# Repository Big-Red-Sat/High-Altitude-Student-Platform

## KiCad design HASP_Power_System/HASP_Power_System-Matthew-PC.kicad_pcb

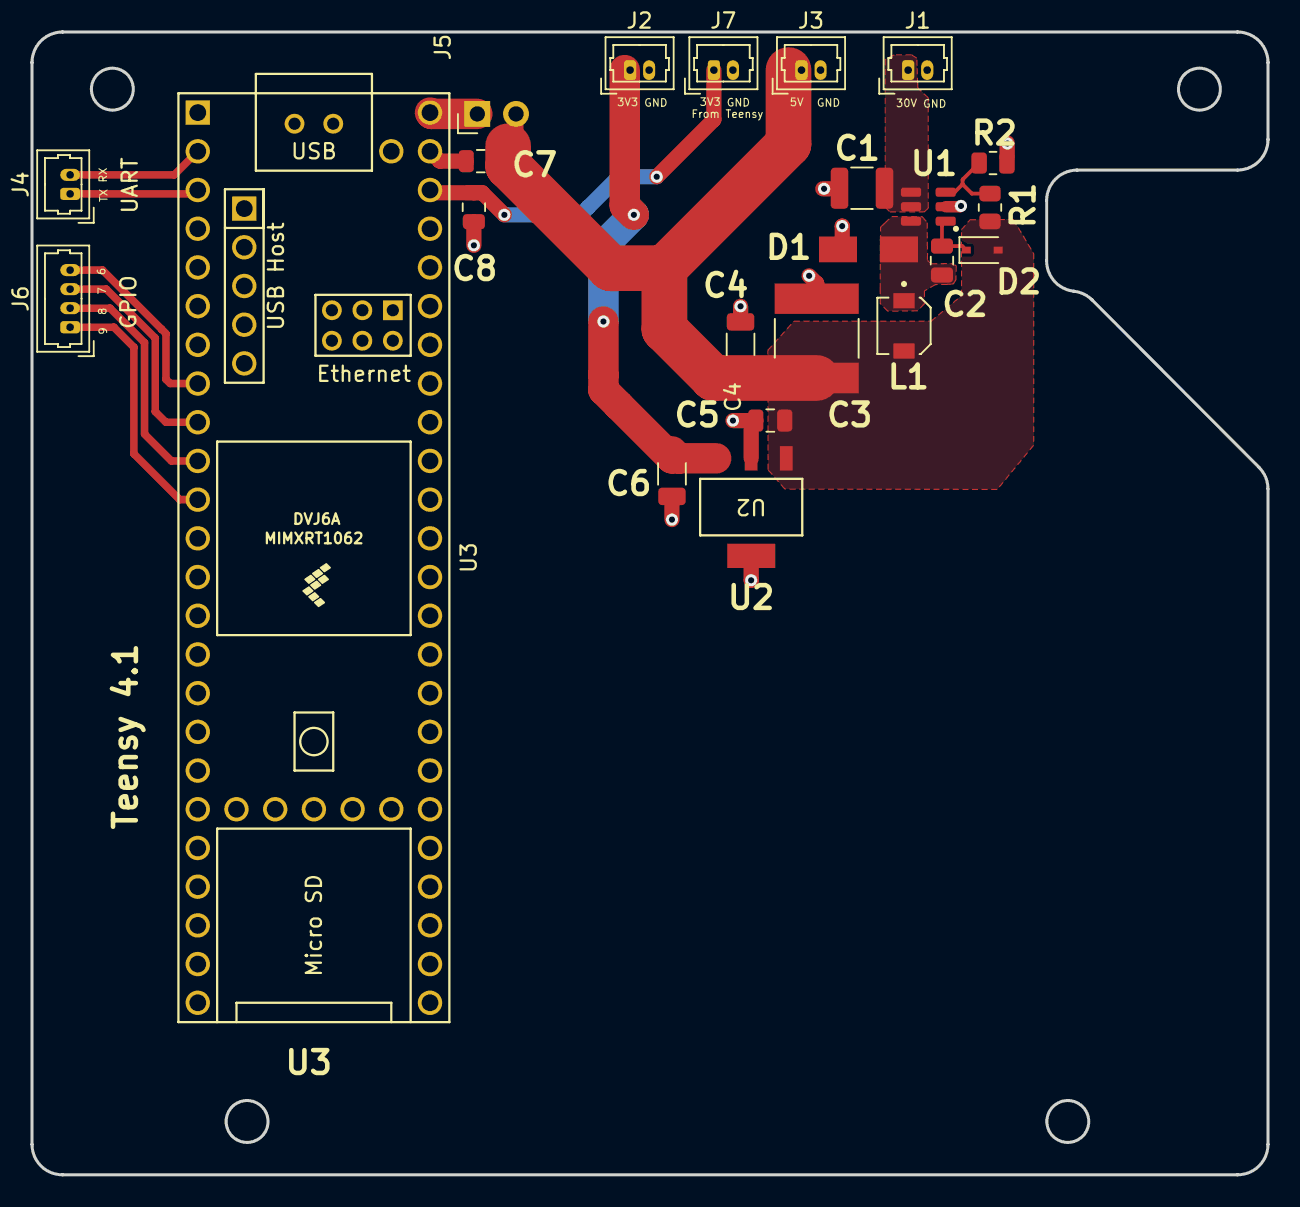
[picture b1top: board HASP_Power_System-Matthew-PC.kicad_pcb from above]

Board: 2 copper layers, 81.1 x 75.0 mm, 23 parts (0 on the bottom side), 15 nets.

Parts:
C1: 10uF; C_1210_3225Metric
C2: 100nF; C_0805_2012Metric
C3: KRM55TR71H226MH01K; CAPC6153X500N
C4: 10uF; C_1206_3216Metric
C5: 0.47uF; C_0805_2012Metric
C6: 33uF; C_1206_3216Metric
C7, C8: 0.1u; C_0805_2012Metric
D1: D_Schottky; schottky_diode_B140-13-F
D2: 1N4148; D_SOD-323
J1, J2, J3, J4, J7: Conn_01x02; Molex_PicoBlade_53047-0210_1x02_P1.25mm_Vertical
J5: Conn_01x02; PinHeader_1x02_P2.54mm_Horizontal
J6: Conn_01x04; Molex_PicoBlade_53047-0410_1x04_P1.25mm_Vertical
L1: 1231AS-H-150M=P3; IND_1231AS-H-150M=P3
R1: 51.2k; R_0805_2012Metric
R2: 10k; R_0805_2012Metric
U1: mcp16301
U2: LM3940IMPX-3.3/NOPB; MP04A
U3: Teensy4.1; Teensy41

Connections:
+3V3_LDO: C6.1, J2.1, U2.3 (OUT)
+3V3_Teensy: C8.1, J7.1, U3.46 (3V3)
+5V: C3.1, C4.1, C5.1, C7.1, D2.2 (A), J3.1, J5.2, L1.2, R1.1, U2.1 (IN)
/SW_NODE: C2.2, D1.1 (K), L1.1, U1.6 (SW)
GND: C1.2, C3.2, C4.2, C5.2, C6.2, C7.2, C8.2, D1.2 (A), J1.2, J2.2, J3.2, J7.2, R2.2, U1.2 (GND), U2.2 (GND), U3.1 (GND), U3.34 (GND), U3.47 (GND)
GPIO1: J6.4, U3.8 (6_OUT1D)
GPIO2: J6.3, U3.9 (7_RX2_OUT1A)
GPIO3: J6.2, U3.10 (8_TX2_IN1)
GPIO4: J6.1, U3.11 (9_OUT1C)
unnamed: C2.1, D2.1 (K), U1.1 (Boost)
unnamed: J5.1, U3.48 (VIN)
unnamed: R1.2, R2.1, U1.3 (V_{FB})
RX: J4.2, U3.2 (0_RX1_CRX2_CS1)
TX: J4.1, U3.3 (1_TX1_CTX2_MISO1)
VCC_30: C1.1, J1.1, U1.4 (EN), U1.5 (V_{IN})

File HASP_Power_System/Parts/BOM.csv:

Reference,Qty,Value,Footprint,Datasheet
C1,1,10uF,Capacitor_SMD:C_1210_3225Metric,
C2,1,100nF,Capacitor_SMD:C_0805_2012Metric,
C3,1,KRM55TR71H226MH01K,KRM55TR71H226MH01K:CAPC6153X500N,
C4,1,10uF,Capacitor_SMD:C_1206_3216Metric,
C5,1,0.47uF,Capacitor_SMD:C_0805_2012Metric,
C6,1,33uF,Capacitor_SMD:C_1206_3216Metric,https://www.digikey.com/en/products/detail/kyocera-avx/TPSA3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
"C7,C8",2,0.1u,Capacitor_SMD:C_0805_2012Metric,
D1,1,D_Schottky,mcp16301:schottky_diode_B140-13-F,
D2,1,1N4148,Diode_SMD:D_SOD-323,
"J1,J2,J3,J4,J7",5,Conn_01x02,Connector_Molex:Molex_PicoBlade_53047-0210_1x02_P1.25mm_Vertical,
J5,1,Conn_01x02,Connector_PinHeader_2.54mm:PinHeader_1x02_P2.54mm_Horizontal,
J6,1,Conn_01x04,Connector_Molex:Molex_PicoBlade_53047-0410_1x04_P1.25mm_Vertical,
L1,1,1231AS-H-150M=P3,1231AS_H_150M_P3:IND_1231AS-H-150M=P3,
R1,1,51.2k,Resistor_SMD:R_0805_2012Metric,
R2,1,10k,Resistor_SMD:R_0805_2012Metric,
U1,1,mcp16301,mcp16301:mcp16301,
U2,1,LM3940IMPX-3.3/NOPB,MP04A,LM3940IMPX-3.3/NOPB
U3,1,Teensy4.1,Teensy:Teensy41,

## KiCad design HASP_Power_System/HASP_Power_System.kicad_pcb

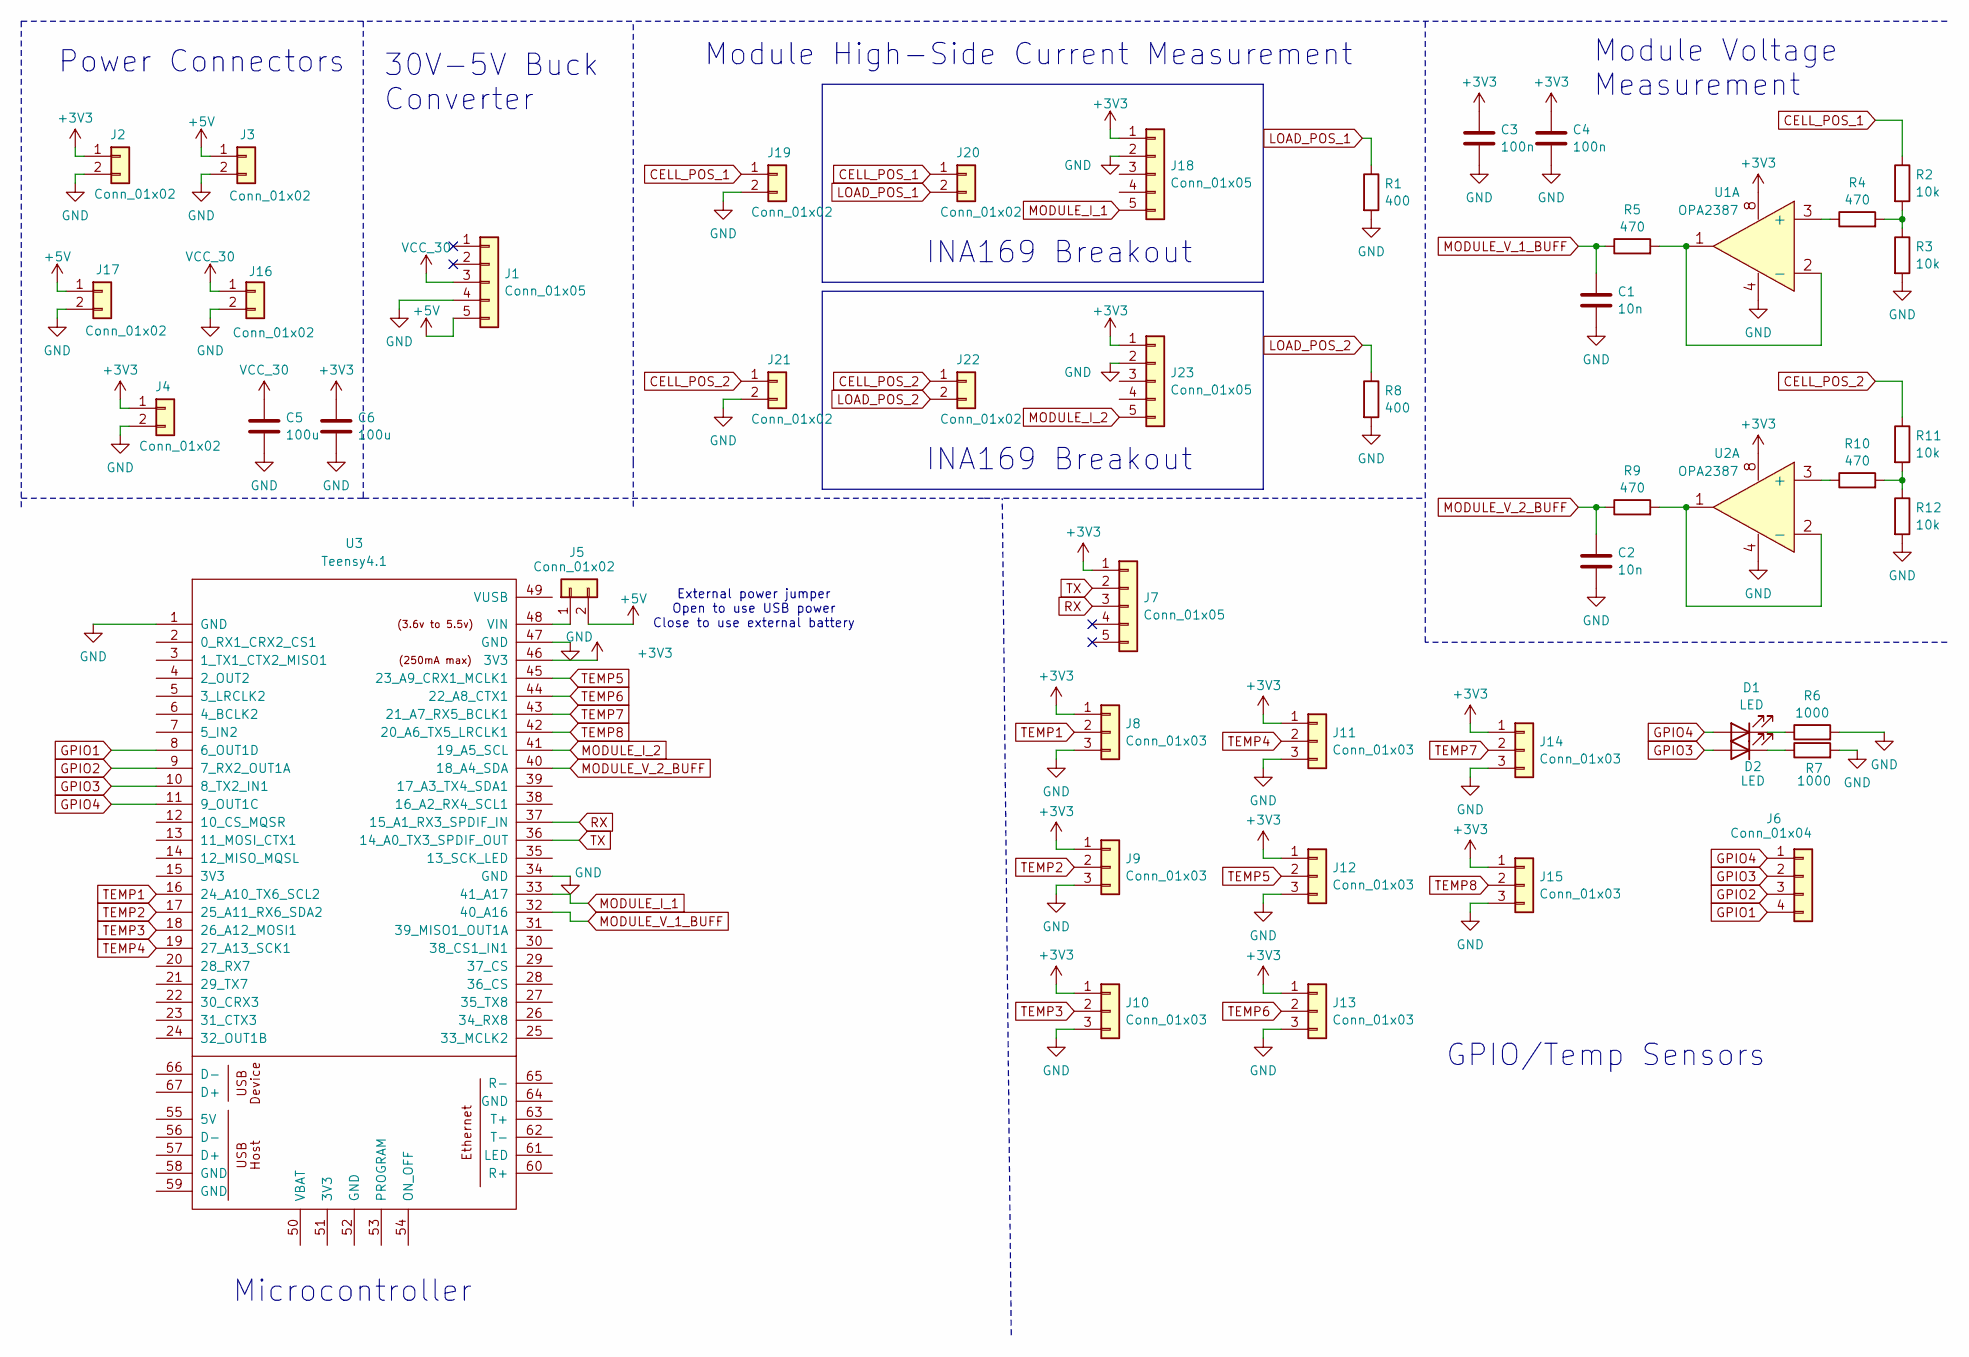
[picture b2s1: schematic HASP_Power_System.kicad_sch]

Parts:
C1, C2: 10n; C_0805_2012Metric
C3, C4: 100n; C_0805_2012Metric
C5, C6: 100u; C_0805_2012Metric
D1, D2: LED; LED_D1.8mm_W3.3mm_H2.4mm
J1: Conn_01x05; PinHeader_1x05_P2.54mm_Vertical
J2, J3, J4, J17, J19, J21: Conn_01x02; Hirose_DF13C_CL535-0402-2-51_1x02-1MP_P1.25mm_Vertical
J5: Conn_01x02; PinSocket_1x02_P2.54mm_Vertical
J6: Conn_01x04; PinHeader_1x04_P2.54mm_Vertical
J7: Conn_01x05; Molex_PicoBlade_53047-0510_1x05_P1.25mm_Vertical
J8, J9, J10, J11, J12, J13, J14, J15: Conn_01x03; PinHeader_1x03_P2.54mm_Vertical
J16: Conn_01x02; AMASS_XT60-M_1x02_P7.20mm_Vertical
J18, J23: Conn_01x05; 1X05_ROUND_70
J20, J22: Conn_01x02; TERMBLOCK_1X2-3.5MM
R1, R8: 400; Load_Resistor_400ohm
R2, R3, R11, R12: 10k; R_0805_2012Metric
R4, R5, R9, R10: 470; R_0805_2012Metric
R6, R7: 1000; R_0805_2012Metric
U1, U2: OPA2387
U3: Teensy4.1; Teensy41

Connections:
+3V3: C3.1, C4.1, C6.1, J2.1, J4.1, J7.1, J8.1, J9.1, J10.1, J11.1, J12.1, J13.1, J14.1, J15.1, J18.1, J23.1, U1.8, U2.8, U3.46 (3V3)
+5V: J1.5, J3.1, J5.2, J17.1
CELL_POS_1: J19.1, J20.1, R2.1
CELL_POS_2: J21.1, J22.1, R11.1
GND: C1.2, C2.2, C3.2, C4.2, C5.2, C6.2, J1.4, J2.2, J3.2, J4.2, J8.3, J9.3, J10.3, J11.3, J12.3, J13.3, J14.3, J15.3, J16.2, J17.2, J18.2, J19.2, J21.2, J23.2, R1.2, R3.2, R6.2, R7.2, R8.2, R12.2, U1.4, U2.4, U3.1 (GND), U3.34 (GND), U3.47 (GND)
GPIO1: J6.4, U3.8 (6_OUT1D)
GPIO2: J6.3, U3.9 (7_RX2_OUT1A)
GPIO3: D2.2 (A), J6.2, U3.10 (8_TX2_IN1)
GPIO4: D1.2 (A), J6.1, U3.11 (9_OUT1C)
LOAD_POS_1: J20.2, R1.1
LOAD_POS_2: J22.2, R8.1
MODULE_I_1: J18.5, U3.33 (41_A17)
MODULE_I_2: J23.5, U3.41 (19_A5_SCL)
MODULE_V_1_BUFF: C1.1, R5.1, U3.32 (40_A16)
MODULE_V_2_BUFF: C2.1, R9.1, U3.40 (18_A4_SDA)
unnamed: D1.1 (K), R6.1
unnamed: D2.1 (K), R7.1
unnamed: J5.1, U3.48 (VIN)
unnamed: R2.2, R3.1, R4.2
unnamed: R10.2, R11.2, R12.1
unnamed: R4.1, U1.3 (+)
unnamed: R5.2, U1.1, U1.2 (-)
unnamed: R10.1, U2.3 (+)
unnamed: R9.2, U2.1, U2.2 (-)
RX: J7.3, U3.37 (15_A1_RX3_SPDIF_IN)
TEMP1: J8.2, U3.16 (24_A10_TX6_SCL2)
TEMP2: J9.2, U3.17 (25_A11_RX6_SDA2)
TEMP3: J10.2, U3.18 (26_A12_MOSI1)
TEMP4: J11.2, U3.19 (27_A13_SCK1)
TEMP5: J12.2, U3.45 (23_A9_CRX1_MCLK1)
TEMP6: J13.2, U3.44 (22_A8_CTX1)
TEMP7: J14.2, U3.43 (21_A7_RX5_BCLK1)
TEMP8: J15.2, U3.42 (20_A6_TX5_LRCLK1)
TX: J7.2, U3.36 (14_A0_TX3_SPDIF_OUT)
VCC_30: C5.1, J1.3, J16.1

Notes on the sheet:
INA169 Breakout
GPIO/Temp Sensors
Module Voltage Measurement
External power jumper Open to use USB power Close to use external battery
30V-5V Buck Converter
Module High-Side Current Measurement
Power Connectors
Microcontroller

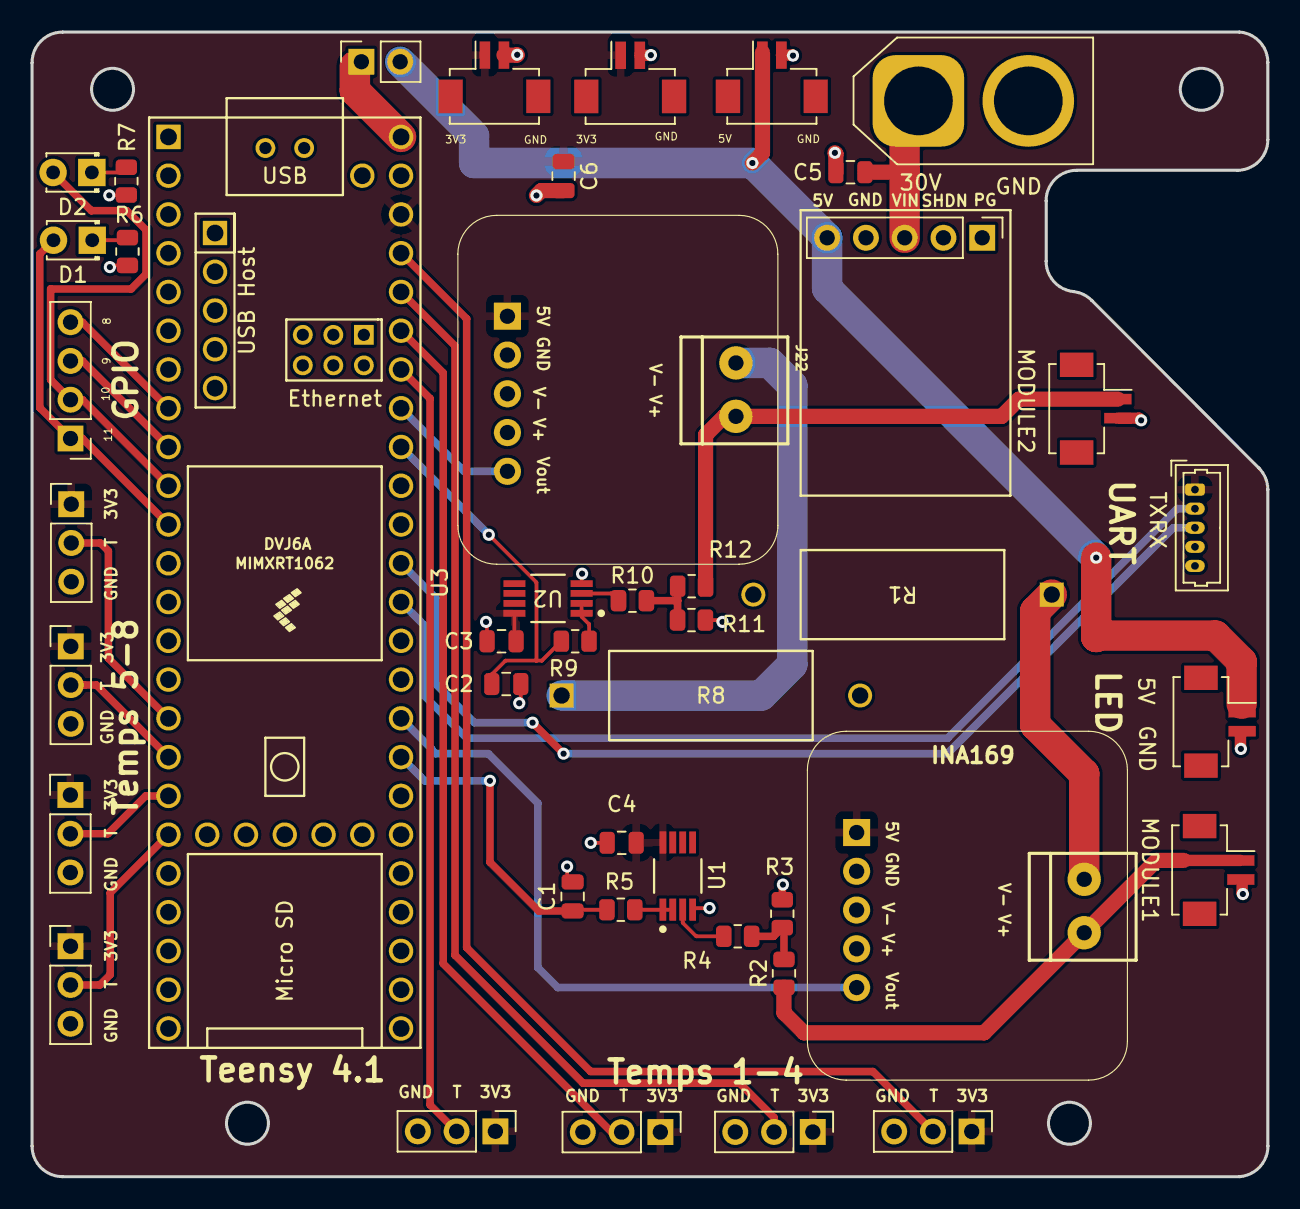
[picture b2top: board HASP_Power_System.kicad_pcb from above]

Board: 2 copper layers, 81.0 x 75.0 mm, 46 parts (0 on the bottom side), 35 nets.

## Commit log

2025-04-24 Create Purpose
    Beginning the official HASP repository
2025-04-24 Initial Characterization
    Characterization 04/24/25 before HAB launch
2025-04-30 Adding HAB Motherboard Design Files
